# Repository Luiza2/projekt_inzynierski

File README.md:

Postępy realizacji pracy inżynierskiej.
Temat: Prędkościomierz z GPS i układem akwizycji danych.

Wykorzystane elementy:
- STM32 NUCLEO-F446RE
- wyświetlacz OLED niebieski graficzny 1,3'' 128x64px SPI
- moduł GPS NEO-7M-C (B) 
- moduł czytnika kart microSD
- moduł bluetooth HC-05
- własna płytka PCB (w opracowaniu)

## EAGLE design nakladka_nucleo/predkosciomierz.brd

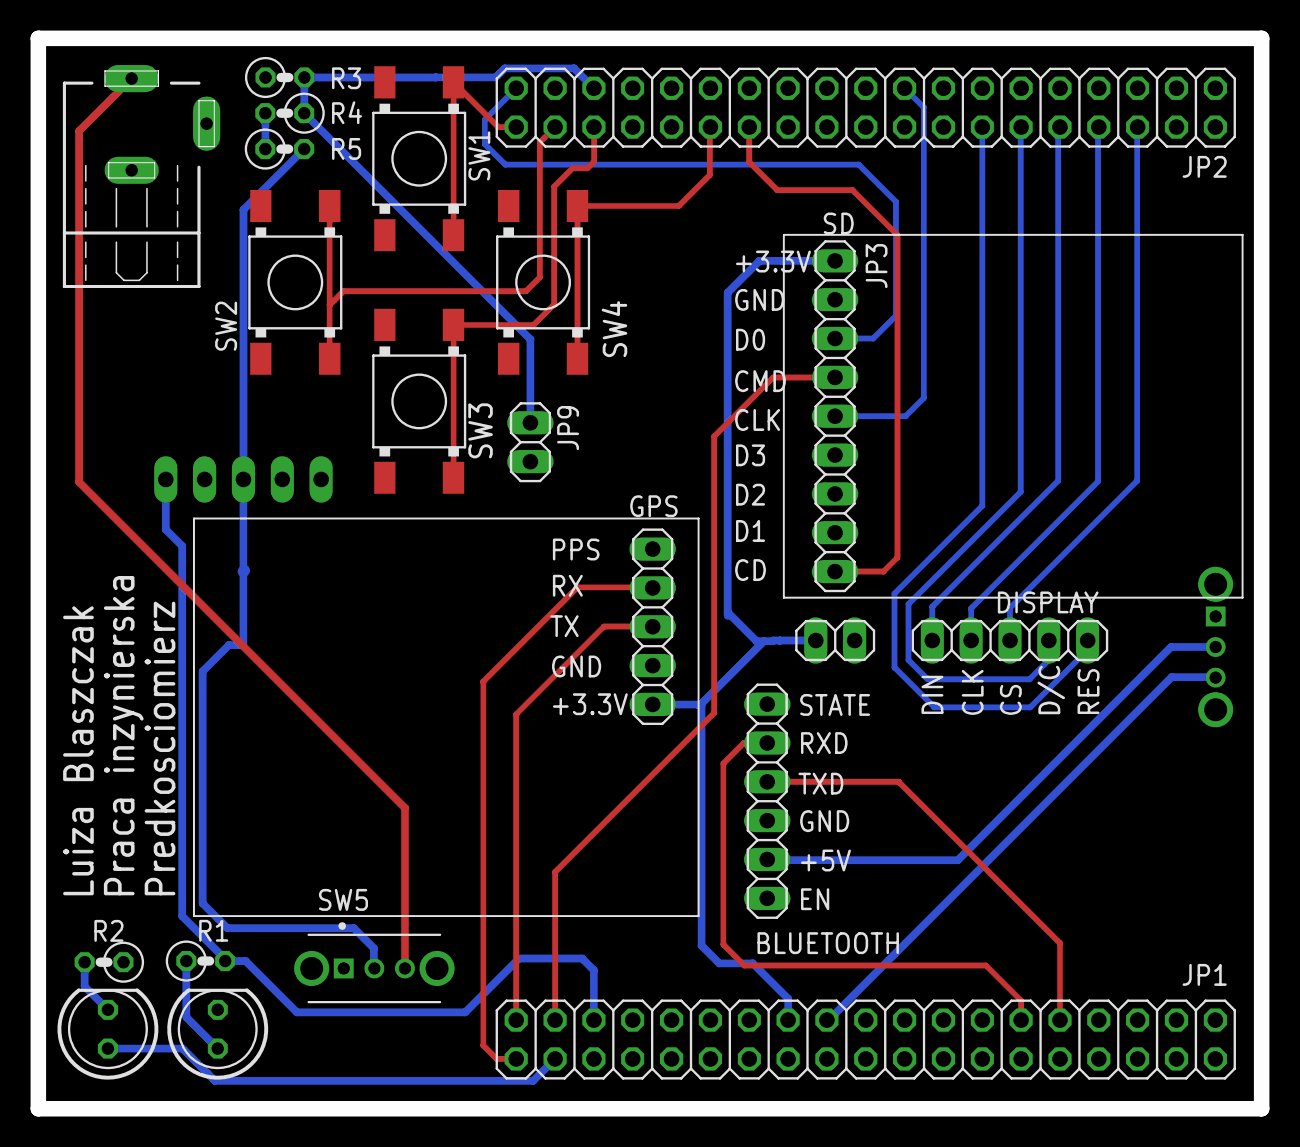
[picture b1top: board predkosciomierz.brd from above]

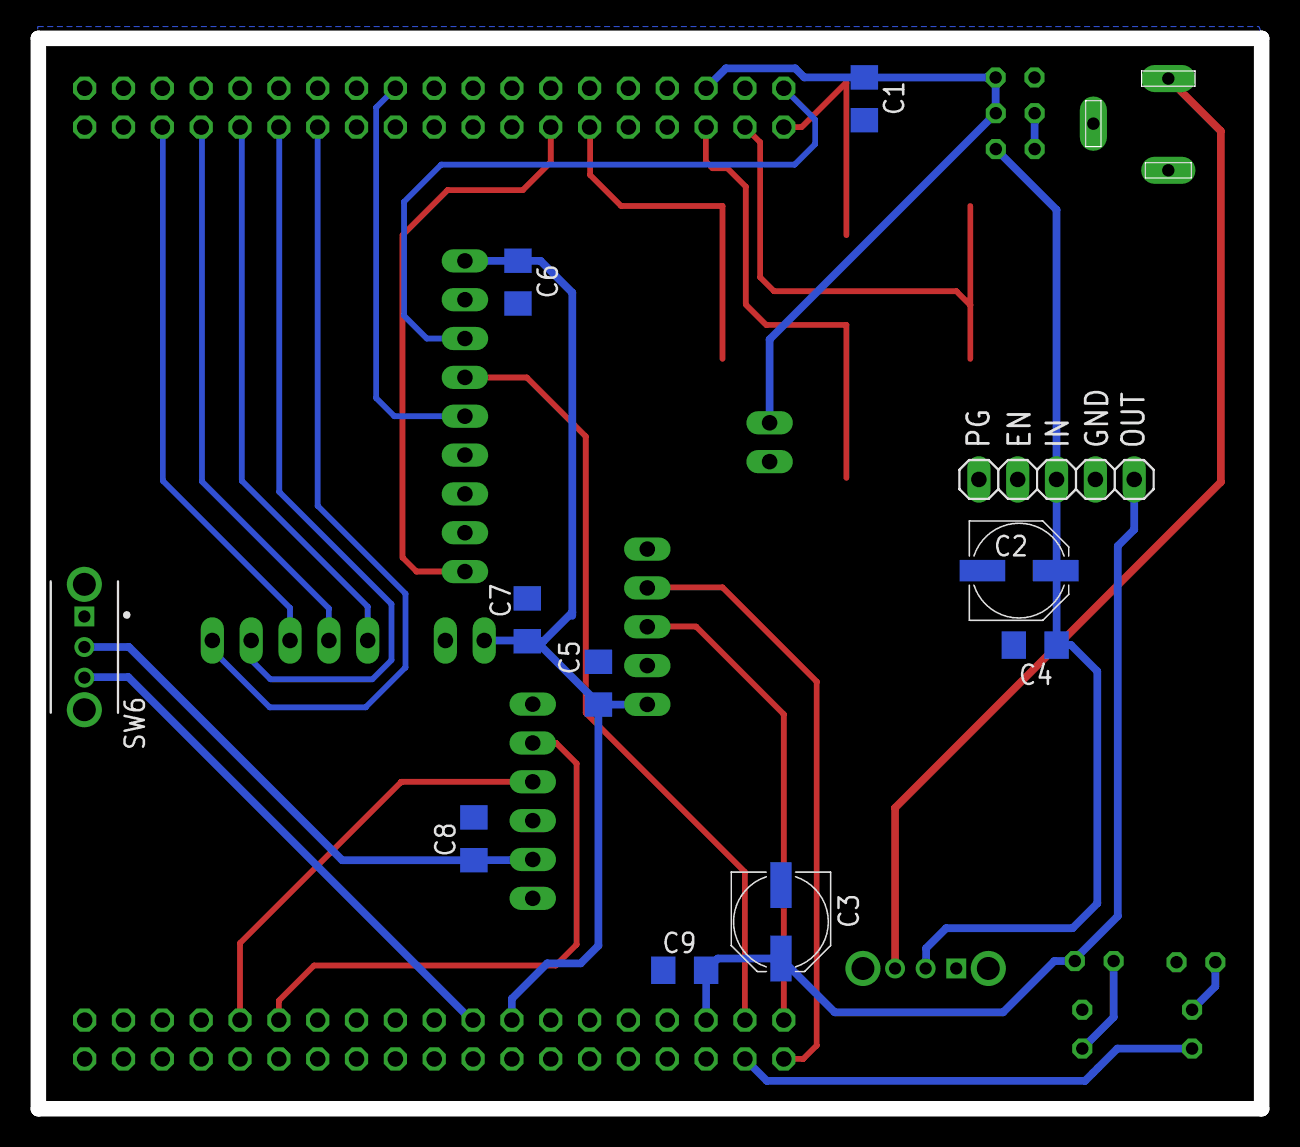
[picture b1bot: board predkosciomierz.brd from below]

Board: 2 copper layers, 80.0 x 70.0 mm, 32 parts (11 on the bottom side), 29 nets.

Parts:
C1, C4, C5, C6, C7, C8, C9: 100n; C1206
C2, C3: 47u; PANASONIC_D
JP1, JP2: 2X19
JP3: 1X09
JP4, JP5, JP8: 1X05
JP7, JP9: 1X02
JP10: 1X06
LED1, LED2: LED5MM
R1, R2: 1k; 0207/2V
R3, R4, R5: 1M; 0207/2V
SW1, SW2, SW3, SW4: LSH
SW5, SW6: C&K_OS102011MA1QN1C&K_OS102011MA1QN1_0_0; C&K_OS102011MA1QN1_0
X1: NEB21R

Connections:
+3.3V: C5.1, C6.1, C7.1, JP1.16, JP3.1, JP5.5, JP7.1
+5V: JP1.18, SW6.3
+5V_IN: C8.1, JP10.5, SW6.2
E5V: C3.+, C9.1, JP1.6, JP4.5, R1.2
GND: C1.2, C2.-, C3.-, C4.2, C5.2, C6.2, C7.2, C8.2, C9.2, JP1.8, JP1.20, JP1.22, JP3.2, JP4.4, JP5.4, JP7.2, JP9.2, JP10.4, LED1.K, R2.1, R3.1, SW1.C1, SW1.C2, SW2.C1, SW2.C2, SW3.C1, SW3.C2, SW4.C1, SW4.C2, SW5.1, SW5.4, SW5.5, SW6.1, SW6.4, SW6.5, X1.2, X1.3
unnamed: LED1.A, R1.1
unnamed: SW5.3, X1.1
unnamed: LED2.K, R2.2
unnamed: R4.2, R5.1
PA0_B_RXD: JP1.28, JP10.2
PA1_B_TXD: JP1.30, JP10.3
PA5_B4_BACK: JP2.11, SW4.NO1, SW4.NO2
PA6_SDIO_CD: JP2.13, JP3.9
PA10_W_CS: JP2.33, JP8.3
PB2_SDIO_CLK: JP2.22, JP3.5
PB3_W_CLK: JP2.31, JP8.2
PB4_W_D/C: JP2.27, JP8.4
PB5_W_DIN: JP2.29, JP8.1
PB8_B2_ENTER: JP2.3, SW2.NO1, SW2.NO2
PB9_B3_PREV: JP2.5, SW3.NO1, SW3.NO2
PB10_W_RES: JP2.25, JP8.5
PC5_ADC: C1.1, JP2.6, JP9.1, R3.2, R4.1
PC8_SDIO_D0: JP2.2, JP3.3
PC9_B1_NEXT: JP2.1, SW1.NO1, SW1.NO2
PC10_GPS_RX: JP1.1, JP5.2
PC11_GPS_TX: JP1.2, JP5.3
PC12_D_BAT: JP1.3, LED2.A
PD2_SDIO_CMD: JP1.4, JP3.4
VIN: C2.+, C4.1, JP4.3, R5.2, SW5.2
